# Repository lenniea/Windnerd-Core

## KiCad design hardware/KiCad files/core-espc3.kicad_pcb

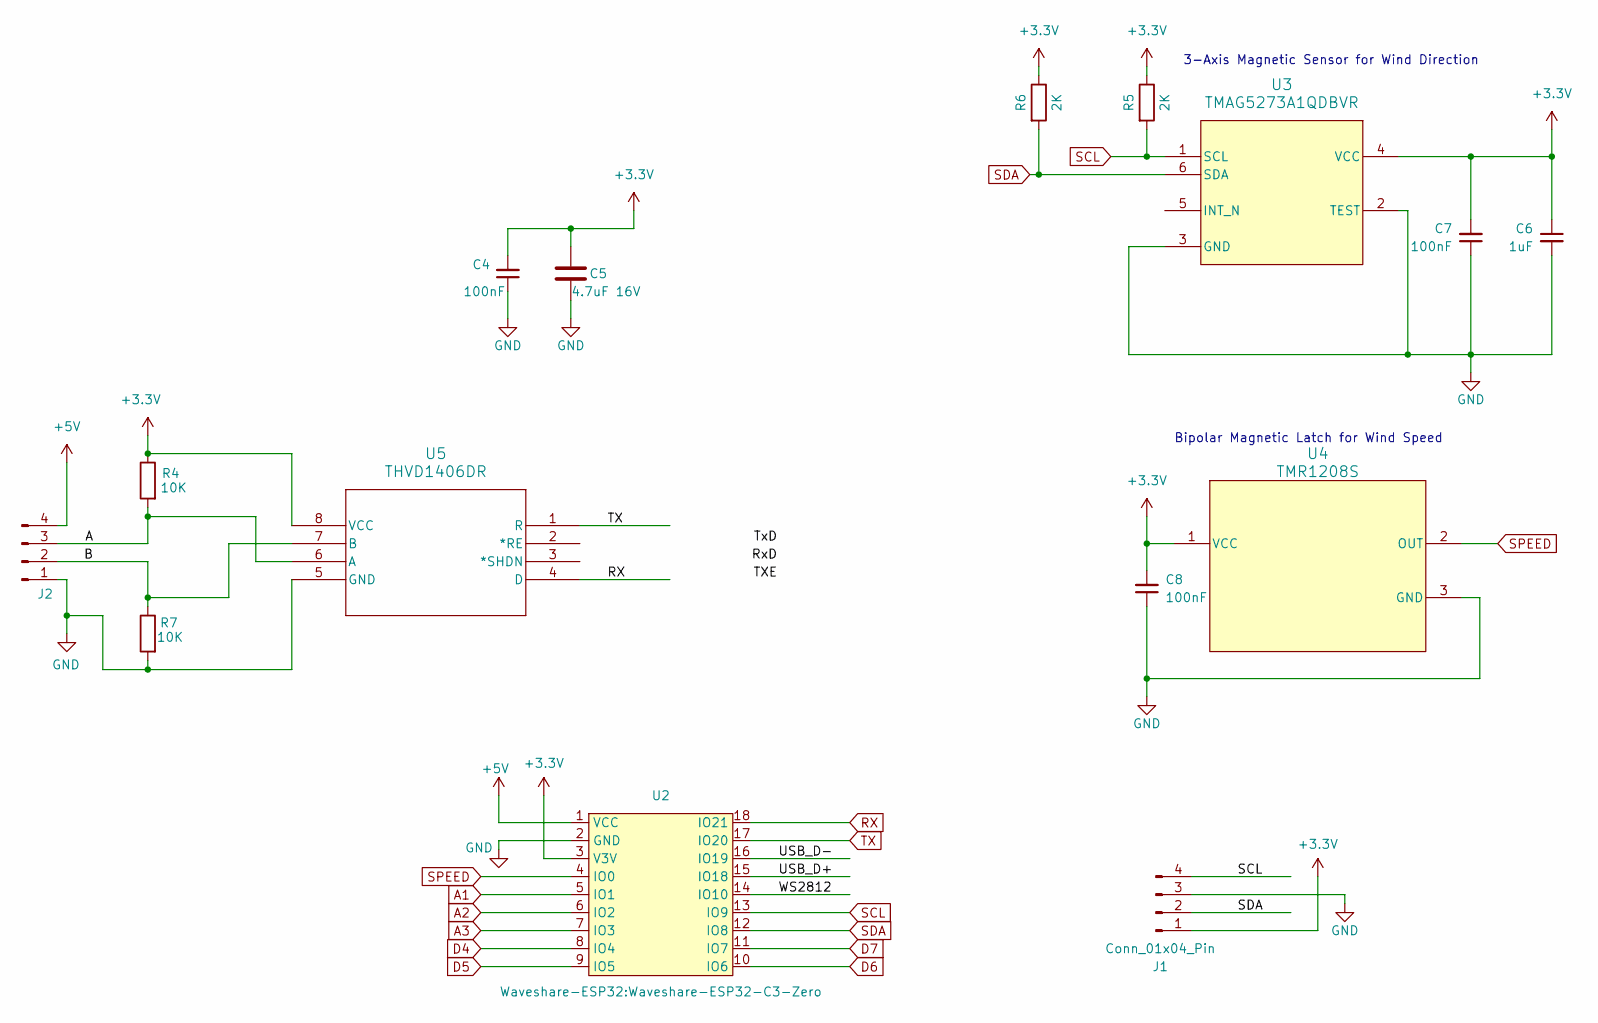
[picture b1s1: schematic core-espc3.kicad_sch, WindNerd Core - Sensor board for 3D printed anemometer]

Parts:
C4: 100nF; C_0603_1608Metric
C5: 4.7uF 16V; C_0603_1608Metric
C6: 1uF; C_0603_1608Metric_Pad1.08x0.95mm_HandSolder
C7, C8: 100nF; C_0603_1608Metric_Pad1.08x0.95mm_HandSolder
J1: Conn_01x04_Pin; PinHeader_1x04_P2.54mm_Vertical
J2: Conn_01x04_Pin; PinHeader_1x04_P2.54mm_Horizontal
R4, R7: 10K; R_0603_1608Metric_Pad0.98x0.95mm_HandSolder
R5, R6: 2K; R_0603_1608Metric_Pad0.98x0.95mm_HandSolder
U2: Waveshare-ESP32-C3-Zero
U3: TMAG5273A1QDBVR; SOT-23-6
U4: TMR1208S; SOT-23
U5: THVD1406DR; SOIC-8_5.3x6.2mm_P1.27mm

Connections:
+3.3V: C4.2, C5.1, C6.1, C7.2, C8.2, J1.1, R4.1, R5.1, R6.1, U2.3 (V3V), U3.4 (VCC), U4.1 (VCC), U5.8 (VCC)
+5V: J2.4, U2.1 (VCC)
/A: J2.3, R4.2, U5.6 (A)
/B: J2.2, R7.1, U5.7 (B)
/USB_D+: U2.15 (IO18)
/USB_D-: U2.16 (IO19)
/WS2812: U2.14 (IO10)
A1: U2.5 (IO1)
A2: U2.6 (IO2)
A3: U2.7 (IO3)
D4: U2.8 (IO4)
D5: U2.9 (IO5)
D6: U2.10 (IO6)
D7: U2.11 (IO7)
GND: C4.1, C5.2, C6.2, C7.1, C8.1, J1.3, J2.1, R7.2, U2.2 (GND), U3.2 (TEST), U3.3 (GND), U4.3 (GND), U5.5 (GND)
RX: U2.18 (IO21), U5.4 (D)
SCL: J1.4, R5.2, U2.13 (IO9), U3.1 (SCL)
SDA: J1.2, R6.2, U2.12 (IO8), U3.6 (SDA)
SPEED: U2.4 (IO0), U4.2 (OUT)
TX: U2.17 (IO20), U5.1 (R)

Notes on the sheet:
3-Axis Magnetic Sensor for Wind Direction
Bipolar Magnetic Latch for Wind Speed

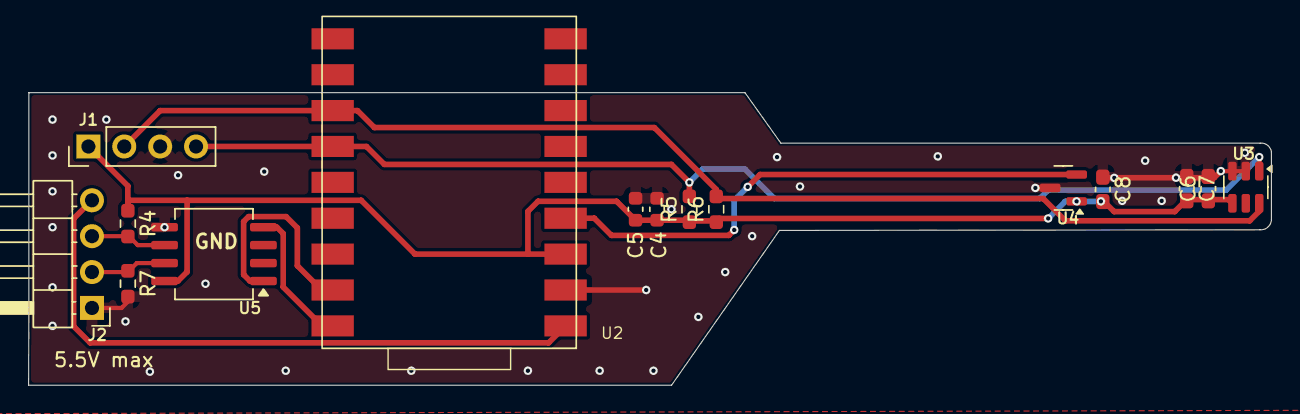
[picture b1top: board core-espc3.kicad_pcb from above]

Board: 2 copper layers, 88.0 x 20.7 mm, 15 parts (0 on the bottom side), 10 nets.

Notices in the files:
hardware/KiCad files/core-espc3.kicad_pcb:
Copyright (c) 2025 windnerd.net
Licensed under CERN Open Hardware License V2 – Strongly Reciprocal (CERN-OHL-S)
